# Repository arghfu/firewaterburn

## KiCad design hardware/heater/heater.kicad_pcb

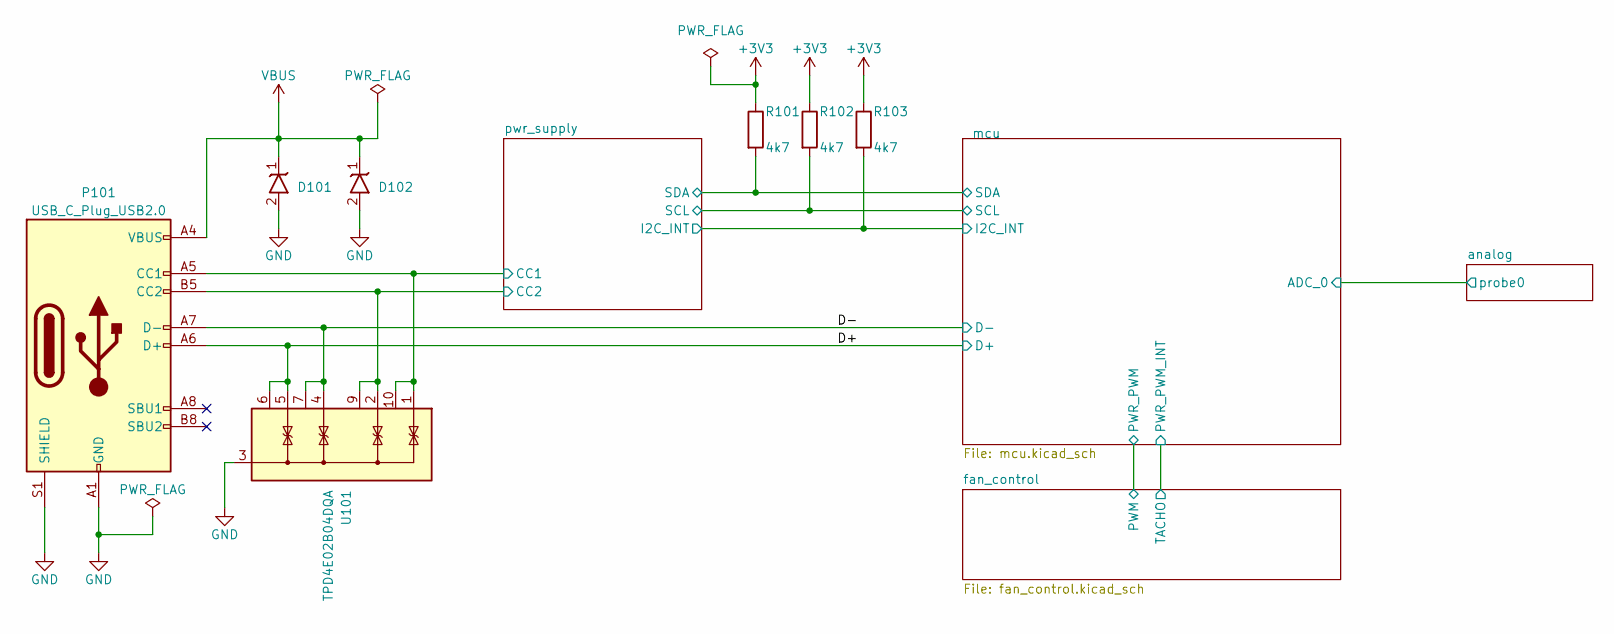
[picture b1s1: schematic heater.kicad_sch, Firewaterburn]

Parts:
D101, D102: ESDA25P35; D_0604_1610Metric; Digikey 497-16913-1-ND
P101: USB_C_Plug_USB2.0; USB_C_Receptacle_Molex_C_24P_SMD_RA; Digikey 900-2171790001CT-ND
R101, R102, R103: 4k7; R_0402_1005Metric; Digikey 13-RC0402FR-134K7LCT-ND
U101: TPD4E02B04DQA; USON-10_2.5x1.0mm_P0.5mm; Digikey 296-43875-1-ND

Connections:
+3V3: R101.1, R102.1, R103.1; also elsewhere on the board
/D+: P101.A6 (D+), P101.B6 (D+), U101.5 (IO4), U101.6 (NC); also elsewhere on the board
/D-: P101.A7 (D-), P101.B7 (D-), U101.4 (IO3), U101.7 (NC); also elsewhere on the board
/mcu/I2C_INT: R103.2; also elsewhere on the board
/mcu/SCL: R102.2; also elsewhere on the board
/mcu/SDA: R101.2; also elsewhere on the board
/pwr_supply/CC1: P101.A5 (CC1), U101.1 (IO1), U101.10 (NC); also elsewhere on the board
/pwr_supply/CC2: P101.B5 (CC2), U101.2 (IO2), U101.9 (NC); also elsewhere on the board
GND: D101.2, D102.2, P101.A1 (GND), P101.A12 (GND), P101.B1 (GND), P101.B12 (GND), P101.S1 (SHIELD), U101.3 (G), U101.8 (G); also elsewhere on the board
VBUS: D101.1, D102.1, P101.A4 (VBUS), P101.A9 (VBUS), P101.B4 (VBUS), P101.B9 (VBUS); also elsewhere on the board

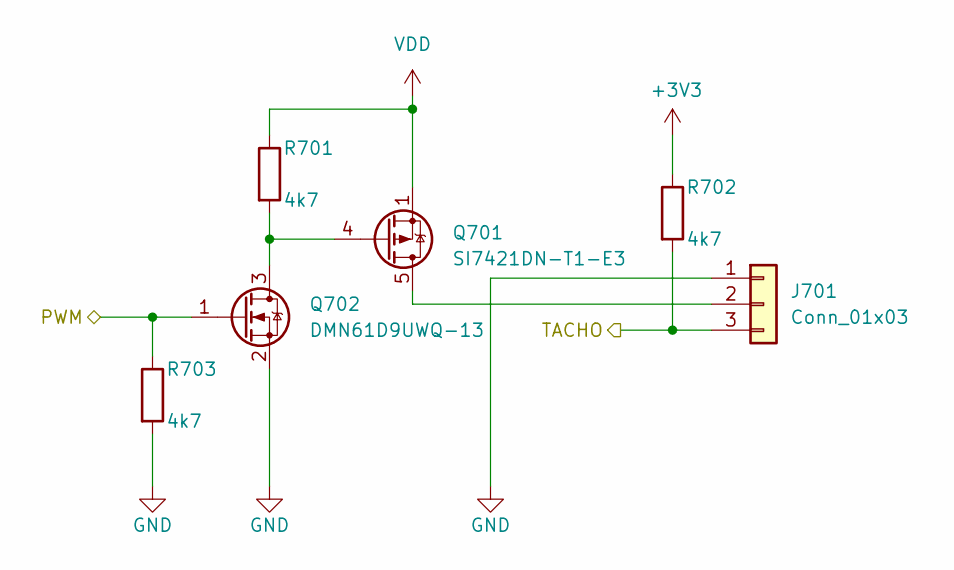
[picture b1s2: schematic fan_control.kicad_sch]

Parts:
J701: Conn_01x03; Molex_Pico-Clasp_202396-0307_1x03-1MP_P1.00mm_Horizontal; Digikey WM26784CT-ND
Q701: SI7421DN-T1-E3; Vishay_PowerPAK_1212-8_Single; Digikey SI7421DN-T1-E3CT-ND
Q702: DMN61D9UWQ-13; SOT-323_SC-70; Digikey DMN61D9UWQ-13DICT-ND
R701, R702, R703: 4k7; R_0603_1608Metric; Digikey 311-4.70KHRCT-ND

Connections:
+3V3: R702.1; also elsewhere on the board
/fan_control/PWM: Q702.1 (G), R703.1; also elsewhere on the board
/fan_control/TACHO: J701.3, R702.2; also elsewhere on the board
GND: J701.1, Q702.2 (S), R703.2; also elsewhere on the board
unnamed: J701.2, Q701.5 (D)
unnamed: Q701.4 (G), Q702.3 (D), R701.2
VDD: Q701.1 (S), Q701.2 (S), Q701.3 (S), R701.1; also elsewhere on the board

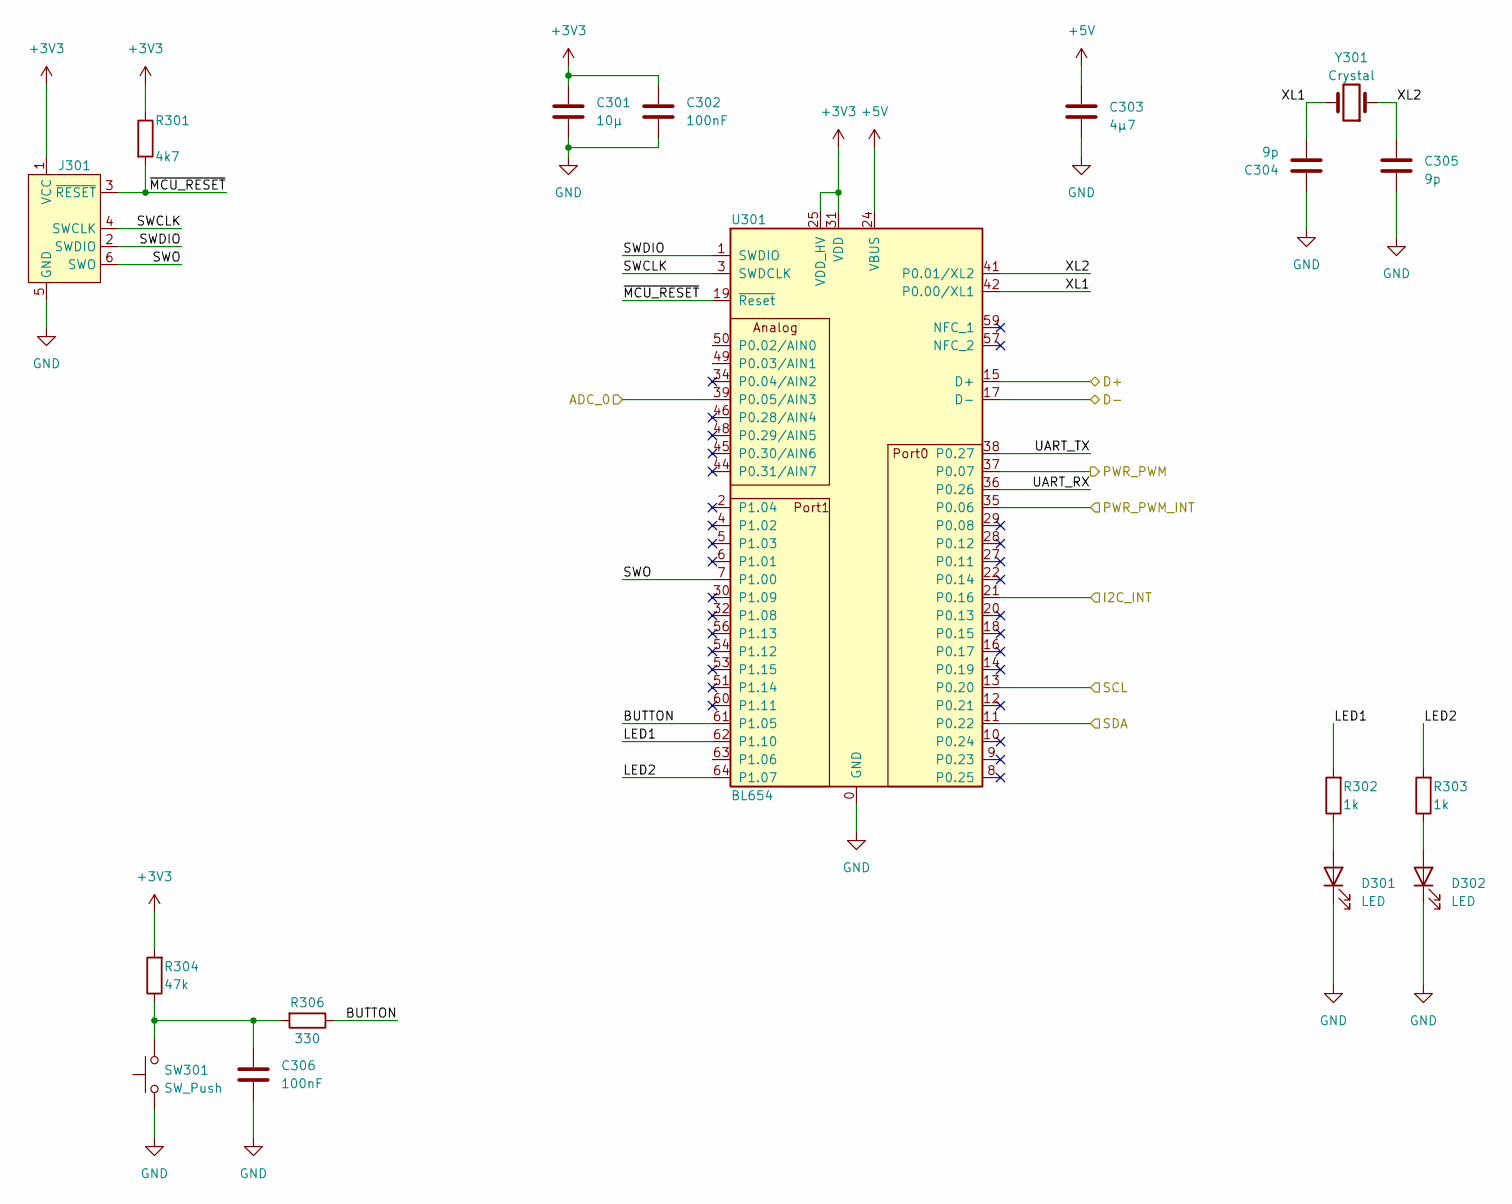
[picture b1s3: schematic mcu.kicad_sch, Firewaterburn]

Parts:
C301: 10µ; C_0603_1608Metric; Digikey 490-18214-1-ND
C302, C306: 100nF; C_0603_1608Metric; Digikey 1276-1006-1-ND
C303: 4µ7; C_0603_1608Metric; Digikey 478-06033D475KAT2ACT-ND
C304, C305: 9p; C_0603_1608Metric; Digikey 445-5627-1-ND
D301, D302: LED; LED_0603_1608Metric; Digikey 516-HSMS-C197CT-ND
J301: Conn_ARM_SWD_TagConnect_TC2030; Tag-Connect_TC2030-IDC-FP_2x03_P1.27mm_Vertical
R301: 4k7; R_0603_1608Metric; Digikey 311-4.70KHRCT-ND
R302, R303: 1k; R_0603_1608Metric; Digikey RNCP0603FTD1K00CT-ND
R304: 47k; R_0603_1608Metric
R306: 330; R_0603_1608Metric
SW301: SW_Push; SW_Push_SPST_NO_Alps_SKRK
U301: BL654; BL654-00001; Digikey 451-00001CT-ND
Y301: Crystal; CM8V-T1A-2Pin_2.0x1.2mm; Digikey 2195-CM8V-T1A-32.768KHZ-9PF-20PPM-TA-QC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

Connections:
+3V3: C301.1, C302.1, J301.1 (VCC), R301.1, R304.2, U301.25 (VDD_HV), U301.31 (VDD); also elsewhere on the board
+5V: C303.1, U301.24 (VBUS); also elsewhere on the board
/D+: U301.15 (D+); also elsewhere on the board
/D-: U301.17 (D-); also elsewhere on the board
/analog/probe0: U301.39 (P0.05/AIN3); also elsewhere on the board
/fan_control/PWM: U301.37 (P0.07); also elsewhere on the board
/fan_control/TACHO: U301.35 (P0.06); also elsewhere on the board
/mcu/BUTTON: R306.1, U301.61 (P1.05)
/mcu/I2C_INT: U301.21 (P0.16); also elsewhere on the board
/mcu/LED1: R302.2, U301.62 (P1.10)
/mcu/LED2: R303.2, U301.64 (P1.07)
/mcu/SCL: U301.13 (P0.20); also elsewhere on the board
/mcu/SDA: U301.11 (P0.22); also elsewhere on the board
/mcu/SWCLK: J301.4 (SWCLK), U301.3 (SWDCLK)
/mcu/SWDIO: J301.2 (SWDIO), U301.1 (SWDIO)
/mcu/SWO: J301.6 (SWO), U301.7 (P1.00)
/mcu/UART_RX: U301.36 (P0.26)
/mcu/UART_TX: U301.38 (P0.27)
/mcu/XL1: C304.2, U301.42 (P0.00/XL1), Y301.2
/mcu/XL2: C305.1, U301.41 (P0.01/XL2), Y301.1
/mcu/~MCU_RESET: J301.3 (~RESET), R301.2, U301.19 (~Reset)
GND: C301.2, C302.2, C303.2, C304.1, C305.2, C306.2, D301.1 (K), D302.1 (K), J301.5 (GND), SW301.1, U301.0 (GND), U301.23 (GND), U301.26 (GND), U301.33 (GND), U301.40 (GND), U301.43 (GND), U301.47 (GND), U301.52 (GND), U301.55 (GND), U301.58 (GND), U301.65 (GND), U301.66 (GND), U301.67 (GND), U301.68 (GND), U301.69 (GND), U301.70 (GND), U301.71 (GND); also elsewhere on the board
unnamed: C306.1, R304.1, R306.2, SW301.2
unnamed: D301.2 (A), R302.1
unnamed: D302.2 (A), R303.1

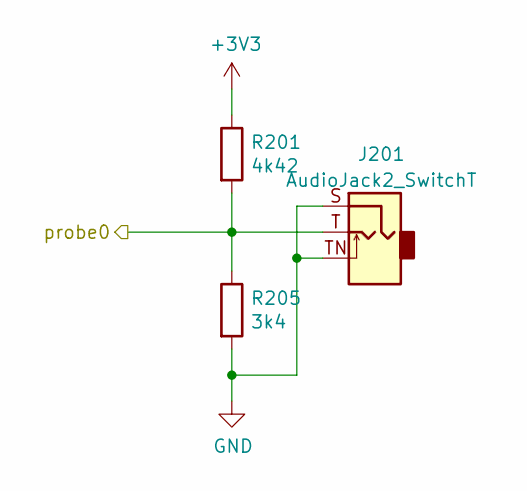
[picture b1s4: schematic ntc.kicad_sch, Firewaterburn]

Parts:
J201: AudioJack2_SwitchT; MJ-2523; Digikey CP-2523MJCT-ND
R201: 4k42; R_0603_1608Metric; Digikey RMCF0603FT4K42CT-ND
R205: 3k4; R_0603_1608Metric; Digikey 311-3.40KHRCT-ND

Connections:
+3V3: R201.1; also elsewhere on the board
/analog/probe0: J201.T, R201.2, R205.1; also elsewhere on the board
GND: J201.S, J201.TN, R205.2; also elsewhere on the board

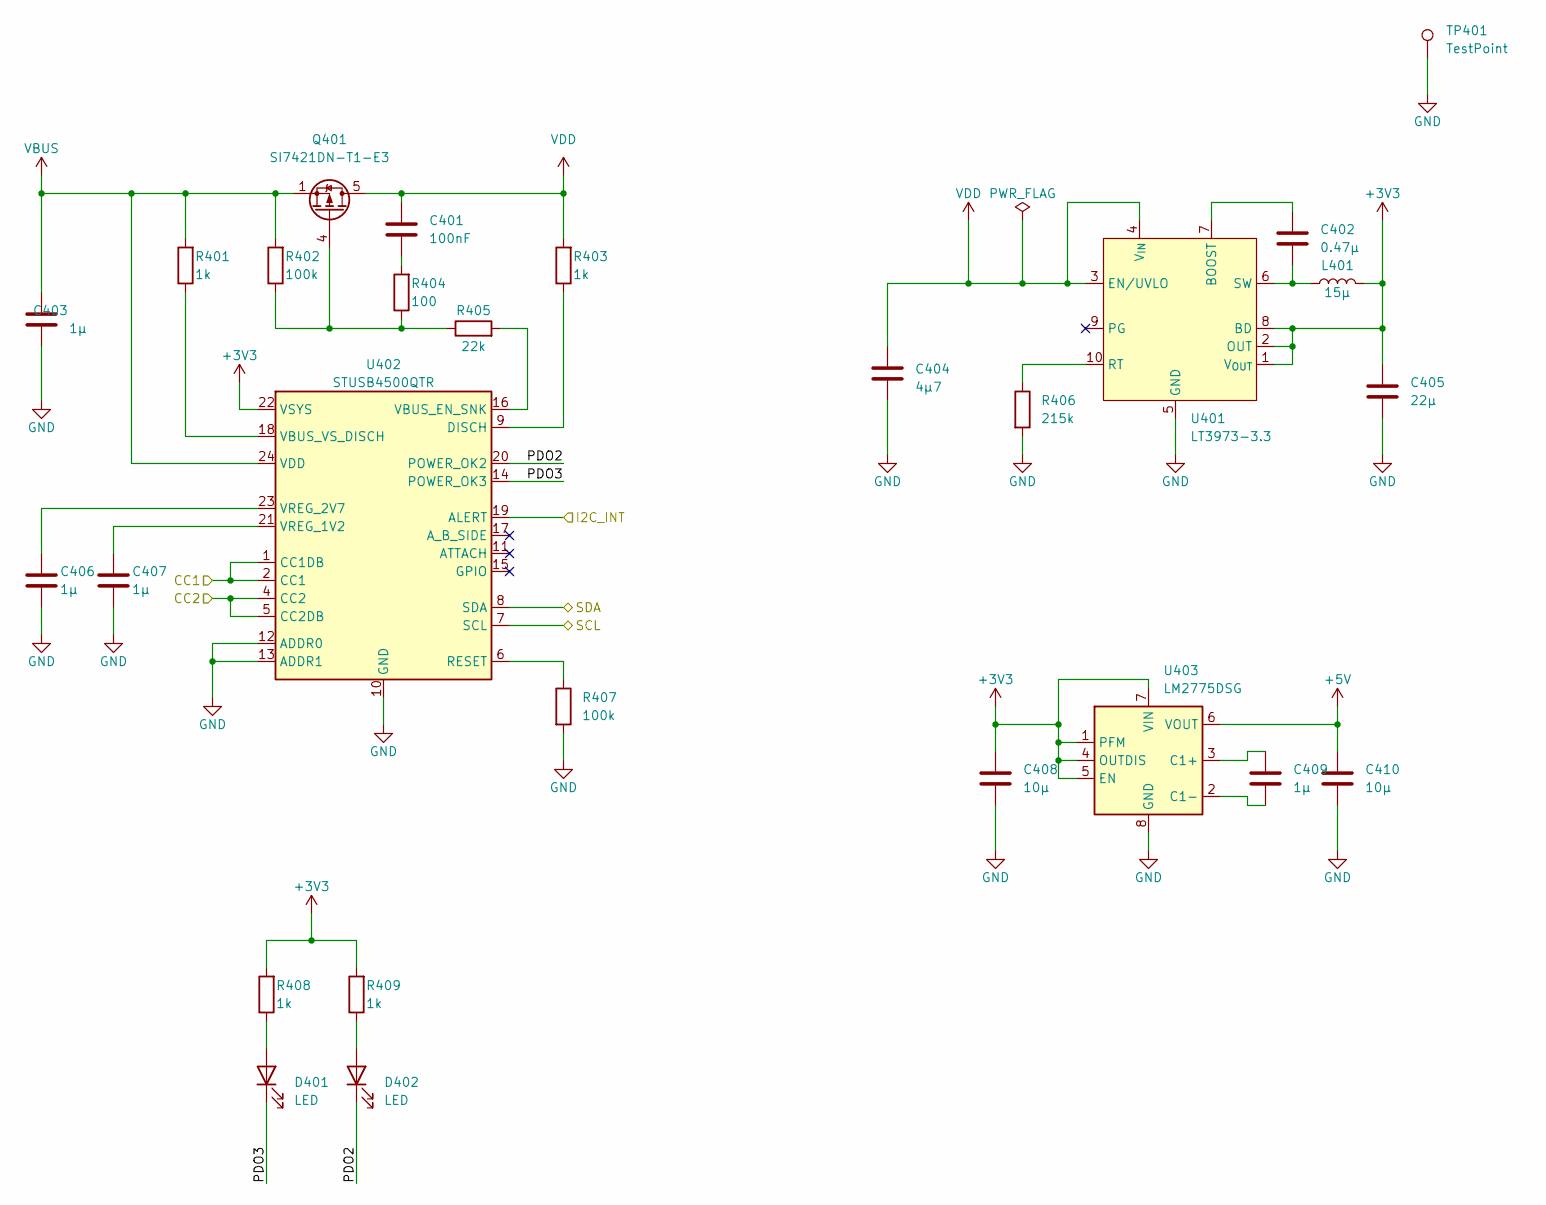
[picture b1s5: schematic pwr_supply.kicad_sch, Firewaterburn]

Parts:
C401: 100nF; C_0603_1608Metric; Digikey 1276-1006-1-ND
C402: 0.47µ; C_0603_1608Metric; Digikey 587-2670-1-ND
C403, C409: 1µ; C_0603_1608Metric; Digikey 1276-1102-1-ND
C404: 4µ7; C_0603_1608Metric; Digikey 478-06033D475KAT2ACT-ND
C405: 22µ; C_0603_1608Metric; Digikey 1276-7076-1-ND
C406, C407: 1µ; C_0402_1005Metric; Digikey 1276-1067-1-ND
C408, C410: 10µ; C_0603_1608Metric; Digikey 490-18214-1-ND
D401, D402: LED; LED_0603_1608Metric; Digikey 516-HSMS-C197CT-ND
L401: 15µ; L_TDK_VLS6045EX_VLS6045AF; Digikey 445-VLS3012HBX-150M-NCT-ND
Q401: SI7421DN-T1-E3; Vishay_PowerPAK_1212-8_Single; Digikey SI7421DN-T1-E3CT-ND
R401, R403: 1k; R_0603_1608Metric; Digikey RNCP0603FTD1K00
R402: 100k; R_0603_1608Metric; Digikey 311-100KHRCT-ND
R404: 100; R_0603_1608Metric; Digikey RNCP0603FTD100RCT-ND
R405: 22k; R_0603_1608Metric; Digikey 10-ERJ-H3EF2202VCT-ND
R406: 215k; R_0603_1608Metric; Digikey YAG5324CT-ND
R407: 100k; R_0402_1005Metric; Digikey 1292-WR04X1003FTLCT-ND
R408, R409: 1k; R_0603_1608Metric; Digikey RNCP0603FTD1K00CT-ND
TP401: TestPoint; TestPoint_Keystone_5015_Micro-Minature; Digikey 36-5015CT-ND
U401: LT3973-3.3; DFN-10-1EP_3x3mm_P0.5mm_EP1.65x2.38mm_ThermalVias; Digikey LT3973IDD-3.3#PBF-ND
U402: STUSB4500QTR; QFN-24-1EP_4x4mm_P0.5mm_EP2.7x2.7mm_ThermalVias; Digikey 497-18060-1-ND
U403: LM2775DSG; WSON-8-1EP_2x2mm_P0.5mm_EP0.9x1.6mm_ThermalVias; Digikey 296-42149-1-ND

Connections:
+3V3: C405.1, C408.1, L401.2, R408.2, R409.2, U401.1 (V_{OUT}), U401.2 (OUT), U401.8 (BD), U402.22 (VSYS), U403.1 (PFM), U403.4 (OUTDIS), U403.5 (EN), U403.7 (VIN); also elsewhere on the board
+5V: C410.1, U403.6 (VOUT); also elsewhere on the board
/mcu/I2C_INT: U402.19 (ALERT); also elsewhere on the board
/mcu/SCL: U402.7 (SCL); also elsewhere on the board
/mcu/SDA: U402.8 (SDA); also elsewhere on the board
/pwr_supply/CC1: U402.1 (CC1DB), U402.2 (CC1); also elsewhere on the board
/pwr_supply/CC2: U402.4 (CC2), U402.5 (CC2DB); also elsewhere on the board
/pwr_supply/PDO2: D402.1 (K), U402.20 (POWER_OK2)
/pwr_supply/PDO3: D401.1 (K), U402.14 (POWER_OK3)
GND: C403.2, C404.2, C405.2, C406.2, C407.2, C408.2, C410.2, R406.2, R407.2, TP401.1, U401.5 (GND), U401.11 (GND), U402.10 (GND), U402.12 (ADDR0), U402.13 (ADDR1), U402.25 (GND), U403.8 (GND), U403.9 (GND); also elsewhere on the board
unnamed: C401.2, R404.2
unnamed: D401.2 (A), R408.1
unnamed: D402.2 (A), R409.1
unnamed: Q401.4 (G), R402.1, R404.1, R405.1
unnamed: C402.1, U401.7 (BOOST)
unnamed: R406.1, U401.10 (RT)
unnamed: C402.2, L401.1, U401.6 (SW)
unnamed: R403.1, U402.9 (DISCH)
unnamed: R407.1, U402.6 (RESET)
unnamed: R405.2, U402.16 (VBUS_EN_SNK)
unnamed: R401.1, U402.18 (VBUS_VS_DISCH)
unnamed: C407.1, U402.21 (VREG_1V2)
unnamed: C406.1, U402.23 (VREG_2V7)
unnamed: C409.2, U403.3 (C1+)
unnamed: C409.1, U403.2 (C1-)
VBUS: C403.1, Q401.1 (S), Q401.2 (S), Q401.3 (S), R401.2, R402.2, U402.24 (VDD); also elsewhere on the board
VDD: C401.1, C404.1, Q401.5 (D), R403.2, U401.3 (EN/UVLO), U401.4 (V_{IN}); also elsewhere on the board

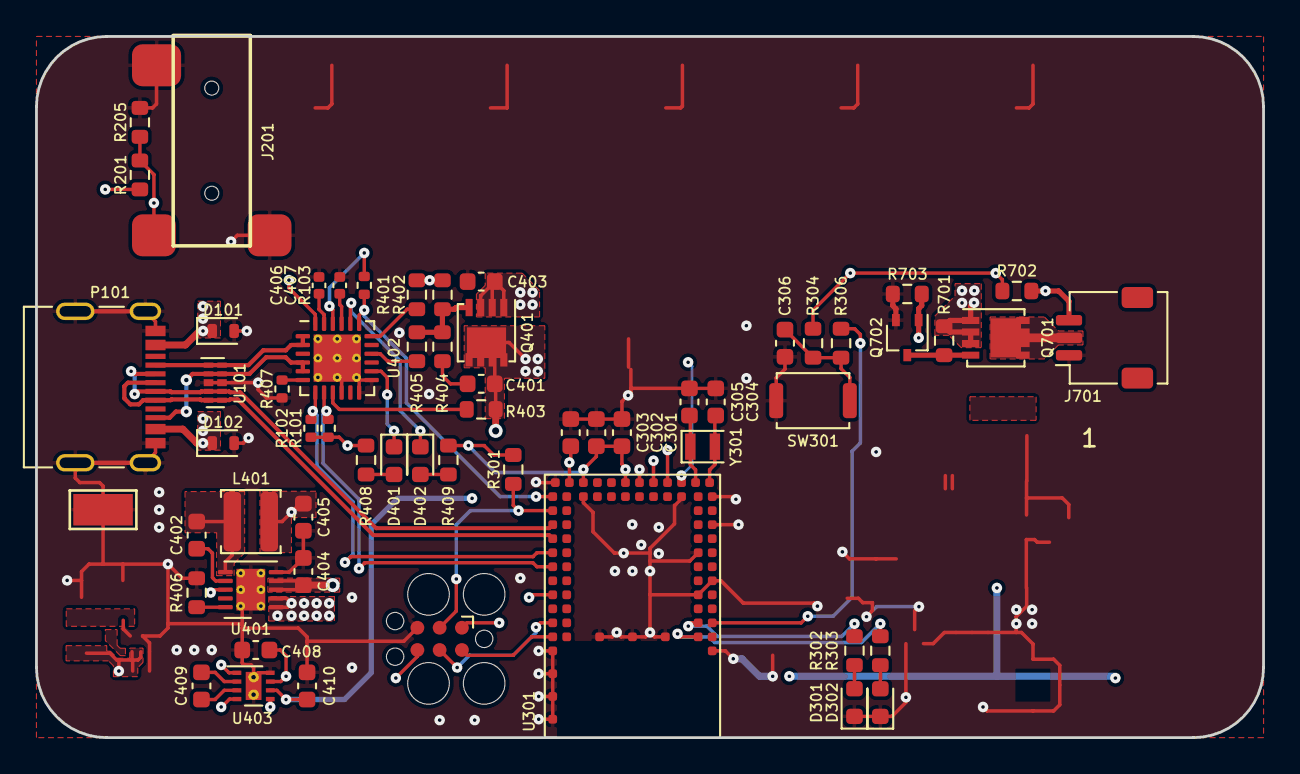
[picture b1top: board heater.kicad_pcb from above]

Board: 4 copper layers, 70.0 x 40.0 mm, 60 parts (0 on the bottom side), 46 nets.

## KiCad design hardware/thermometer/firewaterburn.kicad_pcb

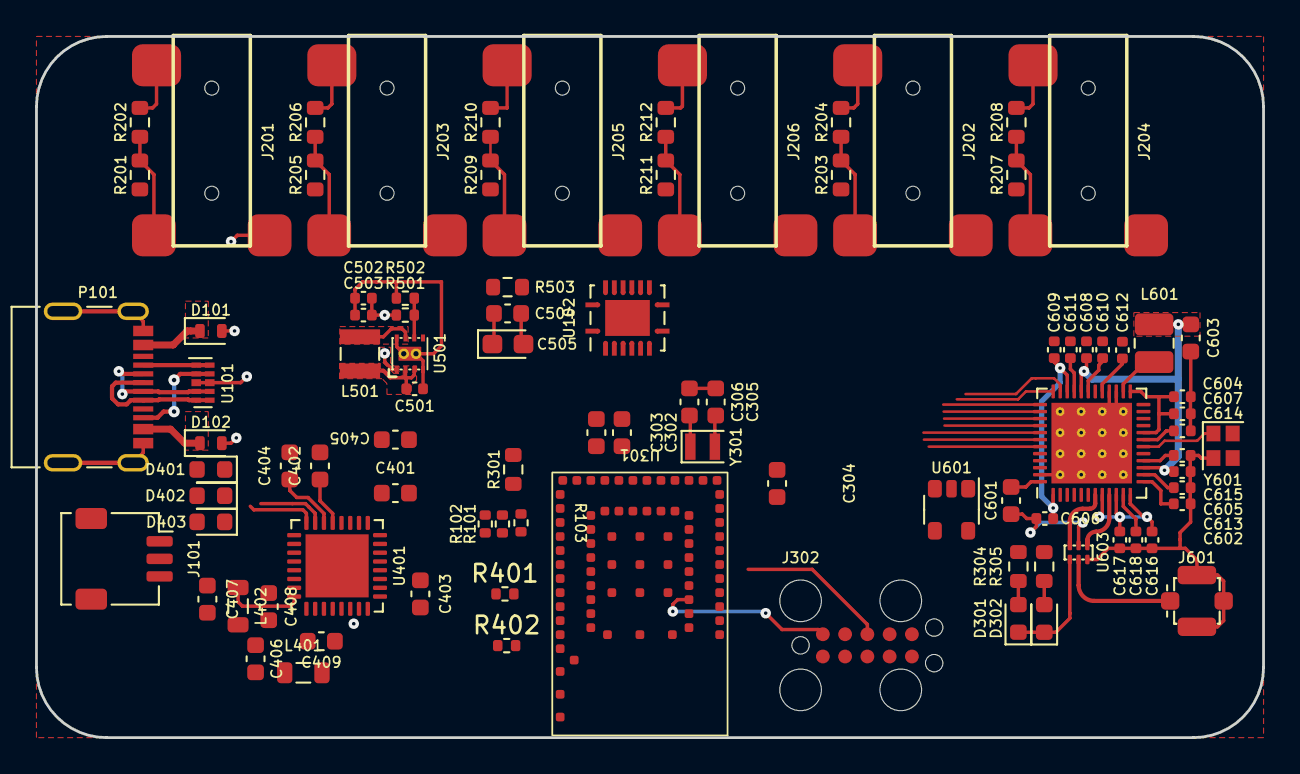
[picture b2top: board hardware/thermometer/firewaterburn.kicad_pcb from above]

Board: 4 copper layers, 70.0 x 40.0 mm, 92 parts (1 on the bottom side), 66 nets.

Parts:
C302, C405, C406, C407, C408, C409: 10µ; C_0603_1608Metric
C303, C403, C504: 100nF; C_0603_1608Metric
C304, C603: 4µ7; C_0603_1608Metric
C305, C306: 9p; C_0603_1608Metric
C401, C601: 2µ2; C_0603_1608Metric
C402, C404: 1µ; C_0603_1608Metric
C501, C607, C611, C614: 1µ; C_0402_1005Metric
C502: 10µ; C_0402_1005Metric
C503: 100nF; C_0402_1005Metric
C505: 4µ7; CP_EIA-2012-15_AVX-P
C602, C604, C616: 4µ7; C_0402_1005Metric
C605: 0.22µ; C_0402_1005Metric
C606, C617: 100n; C_0402_1005Metric
C608, C618: 0.47µ; C_0402_1005Metric
C609, C610, C615: 2µ2; C_0402_1005Metric
C612: 10n; C_0402_1005Metric
C613: 22n; C_0402_1005Metric
D101, D102: ESDA25P35; D_0604_1610Metric
D301, D302, D401, D402, D403: LED; LED_0603_1608Metric
J101: Conn_01x03; Molex_Pico-Clasp_202396-0307_1x03-1MP_P1.00mm_Horizontal
J201, J202, J203, J204, J205, J206: AudioJack2_SwitchT; MJ-2523
J302: TC-2050
J501: EA W128064-XALG; F32R-1A7H1-11031
J601: Conn_Coaxial; CONMHF1-SMD-G-T
L401, L402: 2u2; L_0805_2012Metric
L501: 10µ; L_Wuerth_MAPI-2510
L601: 3µ3; L_1008_2520Metric
P101: USB_C_Plug_USB2.0; USB_C_Receptacle_Molex_C_24P_SMD_RA
R101, R102, R103: 4k7; R_0402_1005Metric
R201, R203, R205, R207, R209, R211: 4k42; R_0603_1608Metric
R202, R204, R206, R208, R210, R212: 3k4; R_0603_1608Metric
R301: 4k7; R_0603_1608Metric
R304, R305: 1k; R_0603_1608Metric
R401: 47k; R_0402_1005Metric
R402: 350k; R_0402_1005Metric
R501: 47k5; R_0402_1005Metric
R502: 5k; R_0402_1005Metric
R503: 910k; R_0603_1608Metric
U101: TPD4E02B04DQA; USON-10_2.5x1.0mm_P0.5mm
U102: TXB0106RGY; Texas_RGY_R-PVQFN-N16_EP2.05x2.55mm
U301: BL5340
U401: QFN-32-1EP_5x5mm_P0.5mm_EP3.6x3.6mm
U501: MIC2290; Micrel_MLF-8-1EP_2x2mm_P0.5mm_EP0.8x1.3mm_ThermalVias
U601: TCK106AF; SOT-25
U602: NRF7002-QFAA-Rx; QFN-48-1EP_6x6mm_P0.4mm_EP4.6x4.6mm_ThermalVias
U603: DPX1608LL80R2455A
Y301: Crystal; CM8V-T1A-2Pin_2.0x1.2mm
Y601: 40MHz; Crystal_SMD_2016-4Pin_2.0x1.6mm

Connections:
+1V8: C302.1, C303.1, C403.1, C406.1, J302.1 (VCC), L401.1, R101.1, R102.1, R103.1, R201.1, R203.1, R205.1, R207.1, R209.1, R211.1, R301.1, U102.2 (V_{CCA}), U102.8 (OE), U301.31 (VDD), U301.35 (VDD_HV), U401.1 (VOUT1), U401.12 (VDDIO), U601.5 (V_{IN})
+3V3: C407.1, C501.1, C602.1, C604.1, C607.1, C610.1, J501.11 (VDD), L402.1, L501.1, U102.15 (V_{CCB}), U401.32 (VOUT2), U501.2 (VIN), U501.3 (EN), U602.13 (VBAT), U602.20 (AFEVBAT), U602.25 (BUCKVBAT), U602.31 (BUCKVBATS)
+5V: C304.1, C404.1, U301.40 (VBUS), U401.22 (VBUSOUT)
+12L: C502.1, C503.1, J501.30 (VCC), R501.1, U501.1 (OUT)
/D+: P101.A6 (D+), P101.B6 (D+), U101.5 (IO4), U101.6 (NC), U301.36 (D+)
/D-: P101.A7 (D-), P101.B7 (D-), U101.4 (IO3), U101.7 (NC), U301.42 (D-)
/analog/probe0: J201.T, R201.2, R202.1
/analog/probe1: J203.T, R205.2, R206.1
/analog/probe2: J205.T, R209.2, R210.1
/analog/probe3: J206.T, R211.2, R212.1
/analog/probe4: J202.T, R203.2, R204.1
/analog/probe5: J204.T, R207.2, R208.1
/mcu/QSPI_CLK: U301.16 (QSPI_CLK), U602.35 (QSPI_CLK)
/mcu/QSPI_IO0: U301.24 (QSPI_IO0), U602.37 (QSPI_DATA0)
/mcu/QSPI_IO1: U301.62 (QSPI_IO1), U602.38 (QSPI_DATA1)
/mcu/QSPI_IO2: U301.18 (QSPI_IO2), U602.39 (QSPI_DATA2)
/mcu/QSPI_IO3: U301.17 (QSPI_IO3), U602.40 (QSPI_DATA3)
/mcu/QSPI_~CS: U301.61 (QSPI_CSN), U602.36 (QSPI_SS)
/mcu/SCL: R102.2, U301.38 (I2C_SCL), U401.14 (SCL)
/mcu/SDA: R101.2, U301.37 (I2C_SDA), U401.13 (SDA)
/mcu/SWCLK: J302.4 (SWCLK), U301.56 (SWDCLK)
/mcu/SWDIO: J302.2 (SWDIO), U301.55 (SWDIO)
/mcu/XL1: C305.2, U301.34 (XL1), Y301.2
/mcu/XL2: C306.1, U301.32 (XL2), Y301.1
/mcu/~MCU_RESET: J302.10 (RESET), R301.2, U301.54 (nRESET)
/pwr_supply/Battery: C401.1, J101.3, U401.19 (VBAT)
/pwr_supply/CC1: P101.A5 (CC1), U101.1 (IO1), U101.10 (NC), U401.23 (CC1)
/pwr_supply/CC2: P101.B5 (CC2), U101.2 (IO2), U101.9 (NC), U401.24 (CC2)
/pwr_supply/LED0: D401.1 (K), U401.25 (LED0)
/pwr_supply/LED1: D402.1 (K), U401.26 (LED1)
/pwr_supply/LED2: D403.1 (K), U401.27 (LED2)
/pwr_supply/NTC: J101.2, U401.18 (NTC)
/tft/CLK: J501.20 (D0), U102.13 (B3)
/tft/D/C: J501.17 (D/C), U102.11 (B5)
/tft/MOSI: J501.21 (D1), U102.12 (B4)
/tft/~CS: J501.15 (CS), U102.14 (B2)
/tft/~RESET: J501.16 (RES), U102.16 (B1)
GND: C302.2, C303.2, C304.2, C305.1, C306.2, C401.2, C402.2, C403.2, C404.2, C405.2, C406.2, C407.2, C408.2, C409.2, C501.2, C502.2, C503.2, C504.2, C505.2, C601.2, C602.2, C603.2, C604.2, C605.2, C606.2, C607.2, C608.2, C609.2, C610.2, C611.2, C612.2, C613.2, C614.2, C615.2, C616.2, C617.2, C618.2, D101.2, D102.2, D301.1 (K), D302.1 (K), J101.1, J201.S, J201.TN, J202.S, J202.TN, J203.S, J203.TN, J204.S, J204.TN, J205.S, J205.TN, J206.S, J206.TN, J302.3 (GND), J302.5 (GND), J501.1 (GND), J501.2 (VSS), J501.12 (BS1), J501.13 (BS2), J501.18 (R/W), J501.19 (E/RD), J501.23 (D3), J501.24 (D4), J501.25 (D5), J501.26 (D6), J501.27 (D7), J501.31 (GND), J601.2 (Ext), P101.A1 (GND), P101.A12 (GND), P101.B1 (GND), P101.B12 (GND), P101.S1 (SHIELD), R202.2, R204.2, R206.2, R208.2, R210.2, R212.2, R401.1, R402.1, R502.2, R503.1, U101.3 (G), U101.8 (G), U102.9 (GND), U102.17 (GND), U301.1 (GND), U301.19 (GND), U301.21 (GND), U301.29 (GND), U301.30 (GND), U301.33 (GND), U301.39 (GND), U301.44 (GND), U301.59 (GND), U301.66 (GND), U301.67 (GND), U301.68 (GND), U301.69 (GND), U301.70 (GND), U301.71 (GND), U301.73 (GND), U301.74 (GND), U301.75 (GND), U401.2 (PVSS1), U401.6 (PVSS2), U401.28 (LSIN1/VINLDO1), U401.29 (LSOUT1/VOUTLDO1), U401.30 (LSIN2/VINLDO2), U401.31 (LSOUT2/VOUTLDO2), U401.33 (AVSS), U501.4 (AGND), U501.8 (PGND), U501.9 (EP_GND), U601.2 (GND), U602.27 (BUCKVSS), U602.28 (BUCKVSS), U602.47 (VSS), U602.49 (VSS), U603.2 (GND), U603.4 (GND), U603.6 (GND), Y601.2, Y601.4
IOVDD: C601.1, U601.1 (V_{OUT}), U602.48 (IOVDD)
unnamed: D301.2 (A), R304.1
unnamed: D302.2 (A), R305.1
unnamed: J501.28 (IREF), R503.2
unnamed: C504.1, C505.1, J501.29 (VCOMH)
unnamed: J601.1 (In), U603.5 (COM)
unnamed: L401.2, U401.3 (SW1)
unnamed: L402.2, U401.5 (SW2)
unnamed: R401.2, U401.17 (VSET1)
unnamed: R402.2, U401.16 (VSET2)
unnamed: R501.2, R502.1, U501.6 (FB)
unnamed: L501.2, U501.7 (SW)
unnamed: C614.1, U602.19 (AFELDO)
unnamed: L601.2, U602.26 (BUCKOUT)
unnamed: C612.1, U602.29 (BUCKVMID)
unnamed: C611.1, U602.33 (DIGVDD)
unnamed: C616.1, C617.1, U602.8 (PAVDD1), U602.10 (PAVDD0), U602.12 (PALDO)
unnamed: C613.1, U602.14 (RFVDD)
unnamed: C618.1, U602.11 (SXLDO)
unnamed: U602.9 (TXRF0), U603.1 (2.4G)
unnamed: U602.7 (TXRF1), U603.3 (5G)
unnamed: C615.1, U602.16 (XOLDO)
unnamed: U602.18 (XON), Y601.1
unnamed: U602.17 (XOP), Y601.3
PWRIOVDD: C606.1, C609.1, U602.1 (OTPVDD), U602.34 (PWRIOVDD)
VAA: C405.1, C408.1, C409.1, D401.2 (A), D402.2 (A), D403.2 (A), U401.4 (PVDD), U401.20 (VSYS)
VBUS: C402.1, D101.1, D102.1, P101.A4 (VBUS), P101.A9 (VBUS), P101.B4 (VBUS), P101.B9 (VBUS), U401.21 (VBUS)
VDD_BUCK: C603.1, C605.1, C608.1, L601.1, U602.15 (RFBUCKVDD), U602.32 (PWRBUCKVDD)

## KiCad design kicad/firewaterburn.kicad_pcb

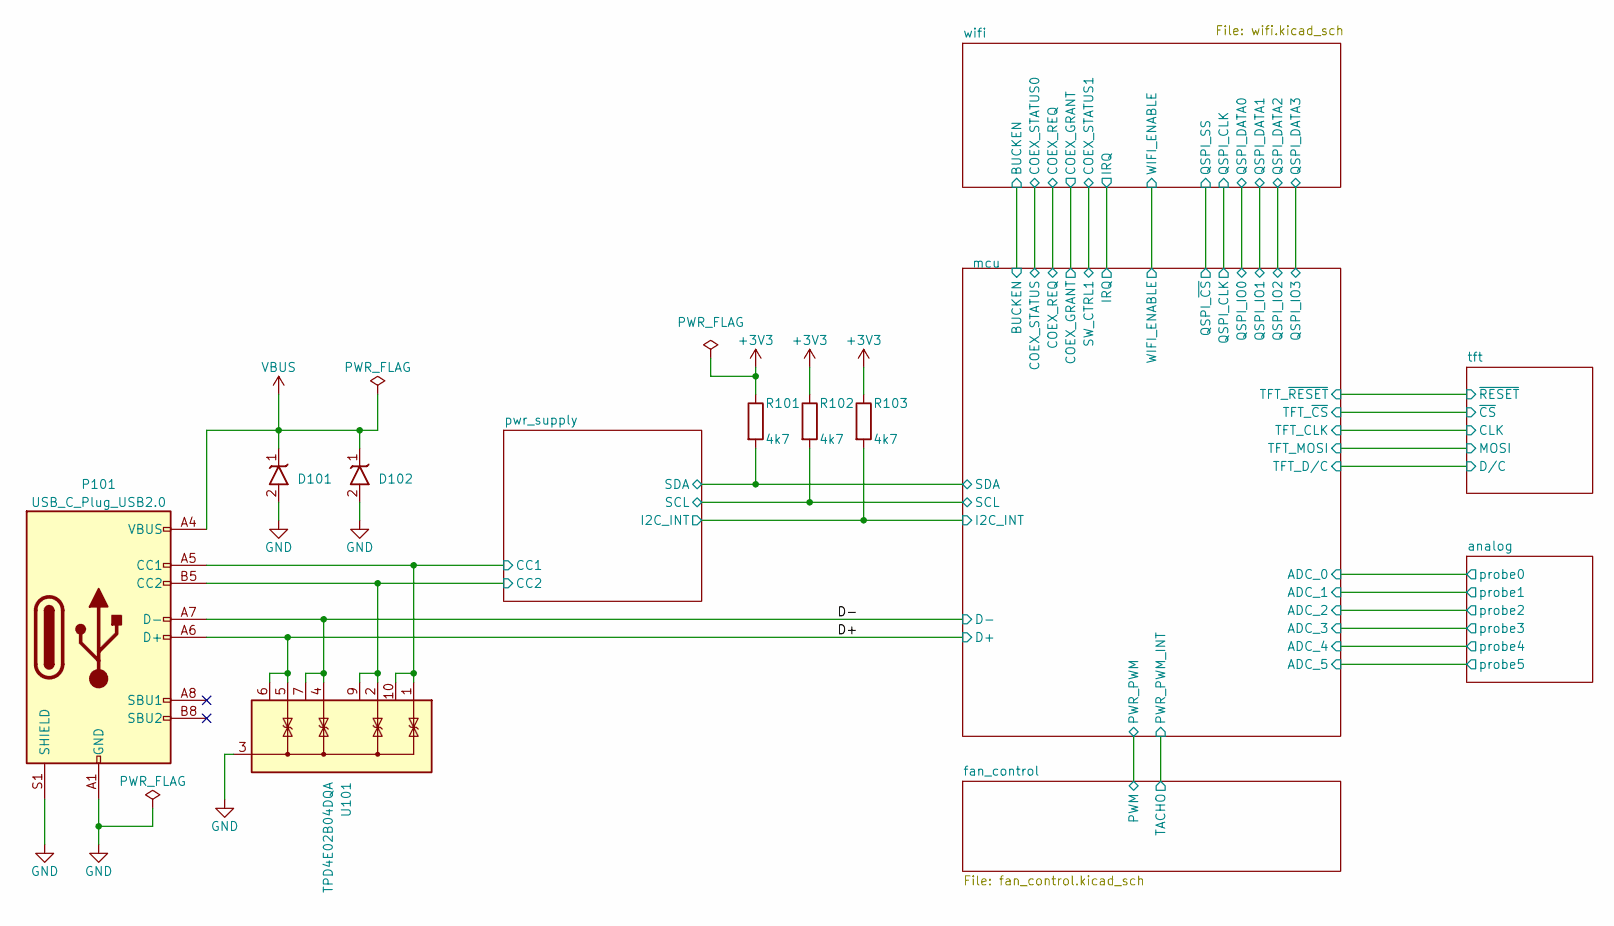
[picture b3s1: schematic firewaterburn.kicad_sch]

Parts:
D101, D102: ESDA25P35; D_0604_1610Metric; Digikey 497-16913-1-ND
P101: USB_C_Plug_USB2.0; USB_C_Receptacle_Molex_C_24P_SMD_RA; Digikey 900-2171790001CT-ND
R101, R102, R103: 4k7; R_0402_1005Metric; Digikey 13-RC0402FR-134K7LCT-ND
U101: TPD4E02B04DQA; USON-10_2.5x1.0mm_P0.5mm; Digikey 296-43875-1-ND

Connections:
+3V3: R101.1, R102.1, R103.1; also elsewhere on the board
/D+: P101.A6 (D+), P101.B6 (D+), U101.5 (IO4), U101.6 (NC); also elsewhere on the board
/D-: P101.A7 (D-), P101.B7 (D-), U101.4 (IO3), U101.7 (NC); also elsewhere on the board
/mcu/I2C_INT: R103.2; also elsewhere on the board
/mcu/SCL: R102.2; also elsewhere on the board
/mcu/SDA: R101.2; also elsewhere on the board
/pwr_supply/CC1: P101.A5 (CC1), U101.1 (IO1), U101.10 (NC); also elsewhere on the board
/pwr_supply/CC2: P101.B5 (CC2), U101.2 (IO2), U101.9 (NC); also elsewhere on the board
VBUS: D101.1, D102.1, P101.A4 (VBUS), P101.A9 (VBUS), P101.B4 (VBUS), P101.B9 (VBUS); also elsewhere on the board

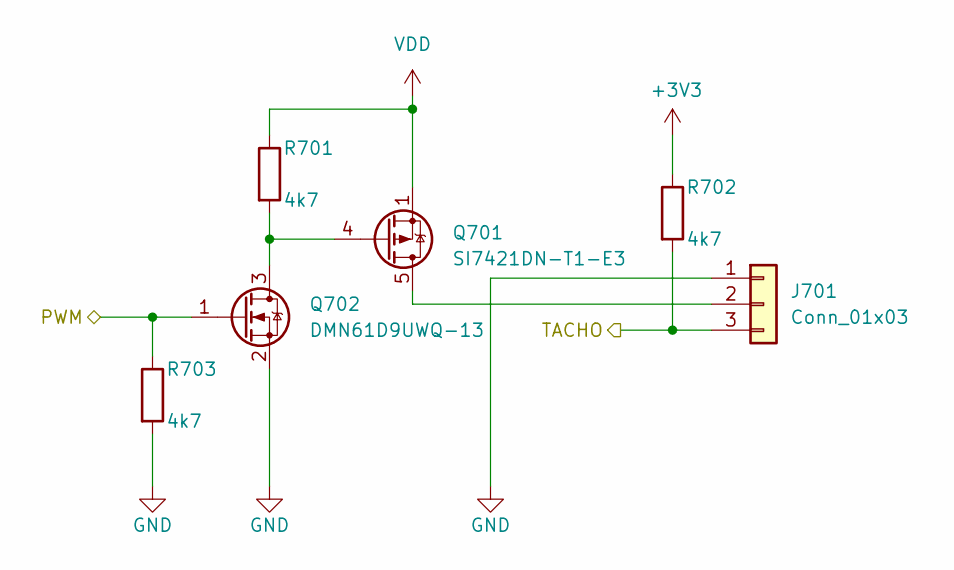
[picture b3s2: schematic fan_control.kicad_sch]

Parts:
J701: Conn_01x03; Molex_Pico-Clasp_202396-0307_1x03-1MP_P1.00mm_Horizontal; Digikey WM26784CT-ND
Q701: SI7421DN-T1-E3; Vishay_PowerPAK_1212-8_Single; Digikey SI7421DN-T1-E3CT-ND
Q702: DMN61D9UWQ-13; SOT-323_SC-70; Digikey DMN61D9UWQ-13DICT-ND
R701, R702, R703: 4k7; R_0603_1608Metric; Digikey 311-4.70KHRCT-ND

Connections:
+3V3: R702.1; also elsewhere on the board
/fan_control/PWM: Q702.1 (G), R703.1; also elsewhere on the board
/fan_control/TACHO: J701.3, R702.2; also elsewhere on the board
unnamed: J701.2, Q701.5 (D)
unnamed: Q701.4 (G), Q702.3 (D), R701.2
VDD: Q701.1 (S), Q701.2 (S), Q701.3 (S), R701.1; also elsewhere on the board

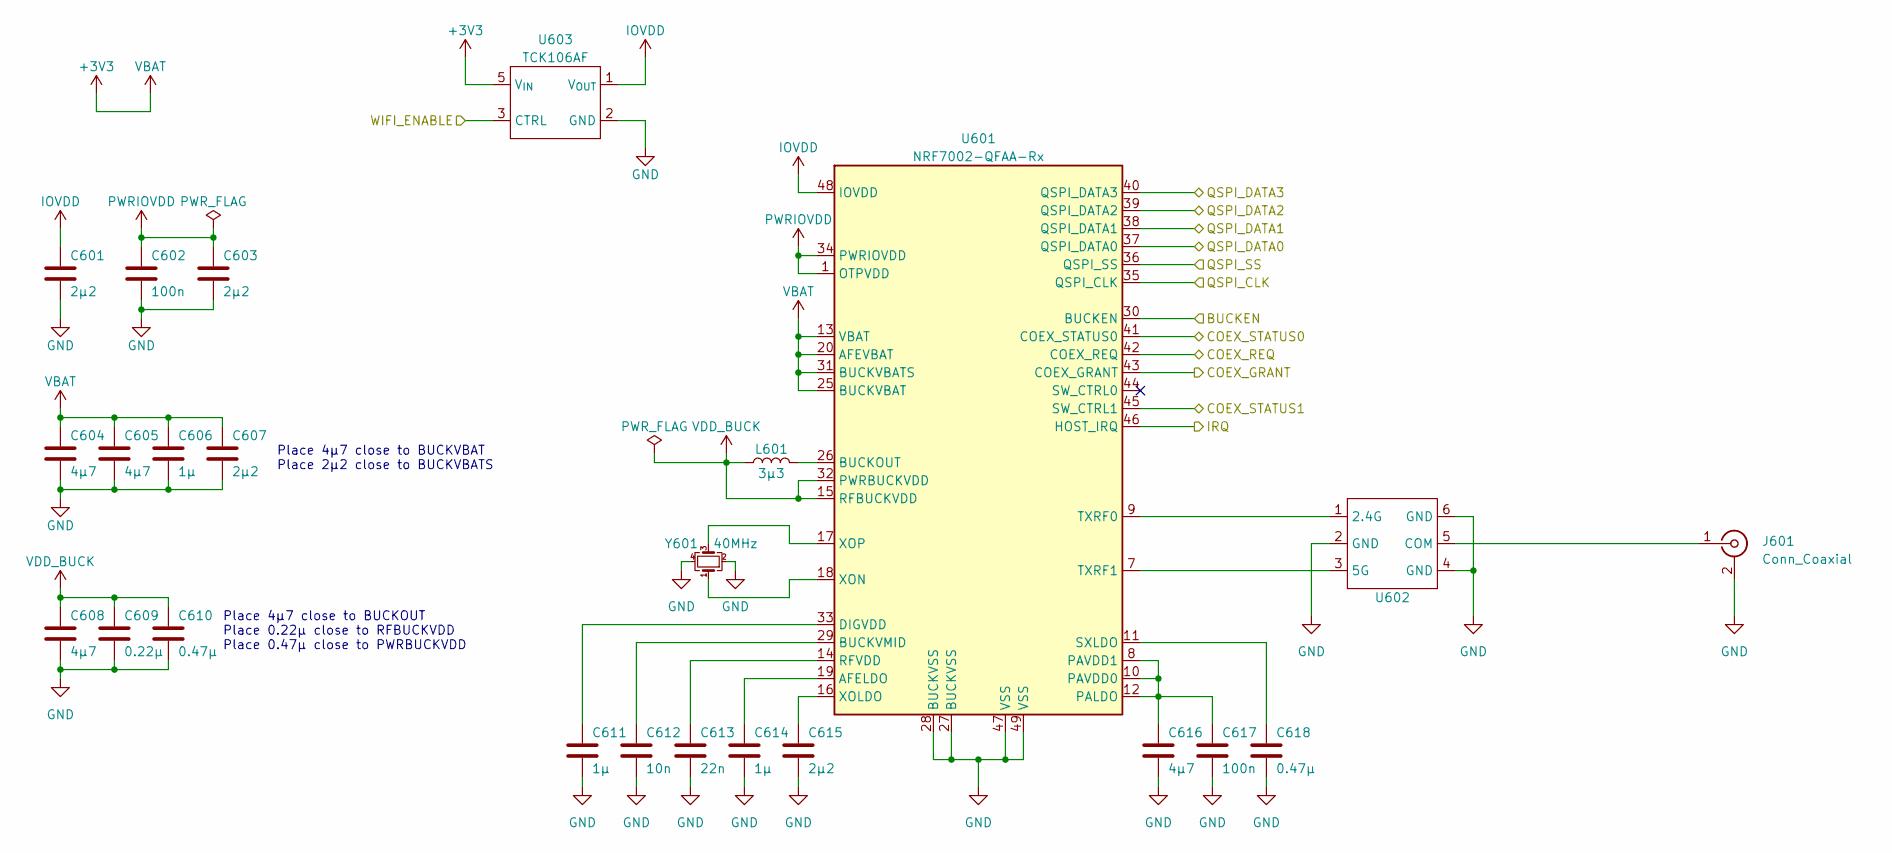
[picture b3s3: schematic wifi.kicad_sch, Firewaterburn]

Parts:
C601: 2µ2; C_0603_1608Metric; Digikey 1276-1040-1-ND
C602, C617: 100n; C_0402_1005Metric; Digikey 478-7888-1-ND
C603, C607, C615: 2µ2; C_0402_1005Metric; Digikey 445-9090-1-ND
C604, C605, C616: 4µ7; C_0402_1005Metric; Digikey 490-GRM155C61E475ME15DCT-ND
C606, C611, C614: 1µ; C_0402_1005Metric; Digikey 1276-1067-1-ND
C608: 4µ7; C_0603_1608Metric; Digikey 490-GRM155C61E475ME15DCT-ND
C609: 0.22µ; C_0402_1005Metric; Digikey 1276-1049-1-ND
C610, C618: 0.47µ; C_0402_1005Metric; Digikey 1276-1477-1-ND
C612: 10n; C_0402_1005Metric; Digikey 1276-1028-1-ND
C613: 22n; C_0402_1005Metric; Digikey 1276-1538-1-ND
J601: Conn_Coaxial; CONMHF1-SMD-G-T; Digikey 343-CONMHF1-SMD-G-TCT-ND
L601: 3µ3; L_1008_2520Metric; Digikey 490-5115-1-ND
U601: NRF7002-QFAA-Rx; QFN-48-1EP_6x6mm_P0.4mm_EP4.6x4.6mm_ThermalVias; Digikey 4823-NRF7002-QFAA-R7CT-ND
U602: DPX1608LL80R2455A; Digikey 553-DPX1608LL80R2455ACT-ND
U603: TCK106AF; SOT-25
Y601: 40MHz; Crystal_SMD_2016-4Pin_2.0x1.6mm; Digikey 478-CX2016DB40000D0FLJCCCT-ND

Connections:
+3V3: C604.1, C605.1, C606.1, C607.1, U601.13 (VBAT), U601.20 (AFEVBAT), U601.25 (BUCKVBAT), U601.31 (BUCKVBATS), U603.5 (V_{IN}); also elsewhere on the board
/mcu/BUCKEN: U601.30 (BUCKEN); also elsewhere on the board
/mcu/COEX_GRANT: U601.43 (COEX_GRANT); also elsewhere on the board
/mcu/COEX_REQ: U601.42 (COEX_REQ); also elsewhere on the board
/mcu/COEX_STATUS: U601.41 (COEX_STATUS0); also elsewhere on the board
/mcu/IRQ: U601.46 (HOST_IRQ); also elsewhere on the board
/mcu/QSPI_CLK: U601.35 (QSPI_CLK); also elsewhere on the board
/mcu/QSPI_IO0: U601.37 (QSPI_DATA0); also elsewhere on the board
/mcu/QSPI_IO1: U601.38 (QSPI_DATA1); also elsewhere on the board
/mcu/QSPI_IO2: U601.39 (QSPI_DATA2); also elsewhere on the board
/mcu/QSPI_IO3: U601.40 (QSPI_DATA3); also elsewhere on the board
/mcu/QSPI_~CS: U601.36 (QSPI_SS); also elsewhere on the board
/mcu/SW_CTRL1: U601.45 (SW_CTRL1); also elsewhere on the board
/mcu/WIFI_ENABLE: U603.3 (CTRL); also elsewhere on the board
IOVDD: C601.1, U601.48 (IOVDD), U603.1 (V_{OUT})
unnamed: J601.1 (In), U602.5 (COM)
unnamed: C614.1, U601.19 (AFELDO)
unnamed: L601.2, U601.26 (BUCKOUT)
unnamed: C612.1, U601.29 (BUCKVMID)
unnamed: C611.1, U601.33 (DIGVDD)
unnamed: C616.1, C617.1, U601.8 (PAVDD1), U601.10 (PAVDD0), U601.12 (PALDO)
unnamed: C613.1, U601.14 (RFVDD)
unnamed: C618.1, U601.11 (SXLDO)
unnamed: U601.9 (TXRF0), U602.1 (2.4G)
unnamed: U601.7 (TXRF1), U602.3 (5G)
unnamed: C615.1, U601.16 (XOLDO)
unnamed: U601.18 (XON), Y601.1
unnamed: U601.17 (XOP), Y601.3
PWRIOVDD: C602.1, C603.1, U601.1 (OTPVDD), U601.34 (PWRIOVDD)
VDD_BUCK: C608.1, C609.1, C610.1, L601.1, U601.15 (RFBUCKVDD), U601.32 (PWRBUCKVDD)

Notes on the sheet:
Place 4µ7 close to BUCKVBAT Place 2µ2 close to BUCKVBATS
Place 4µ7 close to BUCKOUT Place 0.22µ close to RFBUCKVDD Place 0.47µ close to PWRBUCKVDD
